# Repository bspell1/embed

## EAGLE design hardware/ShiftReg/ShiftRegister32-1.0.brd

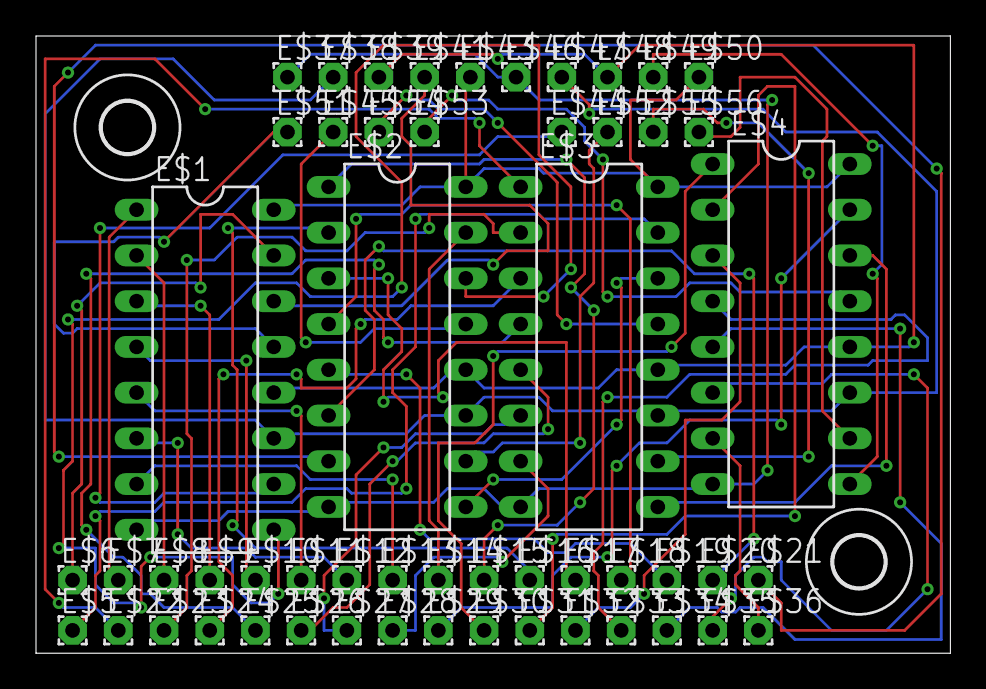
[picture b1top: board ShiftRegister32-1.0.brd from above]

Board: 2 copper layers, 50.8 x 34.3 mm, 56 parts (0 on the bottom side), 49 nets.

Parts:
E$1, E$2, E$3, E$4: 74HC595; DIL16
E$5, E$6, E$7, E$8, E$9, E$10, E$11, E$12, E$13, E$14, E$15, E$16, E$17, E$18, E$19, E$20, E$21, E$22, E$23, E$24, E$25, E$26, E$27, E$28, E$29, E$30, E$31, E$32, E$33, E$34, E$35, E$36, E$37, E$38, E$39, E$41, E$43, E$44, E$45, E$46, E$47, E$48, E$49, E$50, E$51, E$52, E$53, E$54, E$55, E$56: 1,6/0,8
E$40, E$42: 2,8

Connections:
S$1: E$1.8, E$2.8, E$3.8, E$4.8, E$37.1, E$46.1
S$2: E$1.13, E$51.1
S$3: E$1.11, E$2.11, E$3.11, E$4.11, E$38.1, E$47.1
S$4: E$1.12, E$2.12, E$3.12, E$4.12, E$39.1, E$48.1
S$5: E$1.14, E$41.1
S$6: E$1.9, E$2.14
S$7: E$2.9, E$3.14
S$8: E$3.9, E$4.14
S$9: E$1.16, E$2.16, E$3.16, E$4.16, E$43.1, E$50.1
S$10: E$4.9, E$49.1
S$11: E$2.13, E$45.1
S$12: E$3.13, E$54.1
S$13: E$4.13, E$53.1
S$14: E$1.10, E$44.1
S$15: E$2.10, E$52.1
S$16: E$3.10, E$55.1
S$17: E$4.10, E$56.1
S$18: E$1.15, E$6.1
S$19: E$2.15, E$14.1
S$20: E$3.15, E$5.1
S$21: E$4.15, E$29.1
S$22: E$1.1, E$7.1
S$23: E$1.2, E$8.1
S$24: E$1.3, E$9.1
S$25: E$1.4, E$10.1
S$26: E$1.5, E$11.1
S$27: E$1.6, E$12.1
S$28: E$1.7, E$13.1
S$29: E$2.1, E$15.1
S$30: E$2.2, E$16.1
S$31: E$2.3, E$17.1
S$32: E$2.4, E$18.1
S$33: E$2.5, E$19.1
S$34: E$2.6, E$20.1
S$35: E$2.7, E$21.1
S$36: E$3.1, E$22.1
S$37: E$3.2, E$23.1
S$38: E$3.3, E$24.1
S$39: E$3.4, E$25.1
S$40: E$3.5, E$26.1
S$41: E$3.6, E$27.1
S$42: E$3.7, E$28.1
S$43: E$4.1, E$30.1
S$44: E$4.2, E$31.1
S$45: E$4.3, E$32.1
S$46: E$4.4, E$33.1
S$47: E$4.5, E$34.1
S$48: E$4.6, E$35.1
S$49: E$4.7, E$36.1
